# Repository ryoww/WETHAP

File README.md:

[WETHAPのサイト](https://ryoww.github.io/WETHAP/)
実験室の温度・湿度・気圧を教えてくれるツステム

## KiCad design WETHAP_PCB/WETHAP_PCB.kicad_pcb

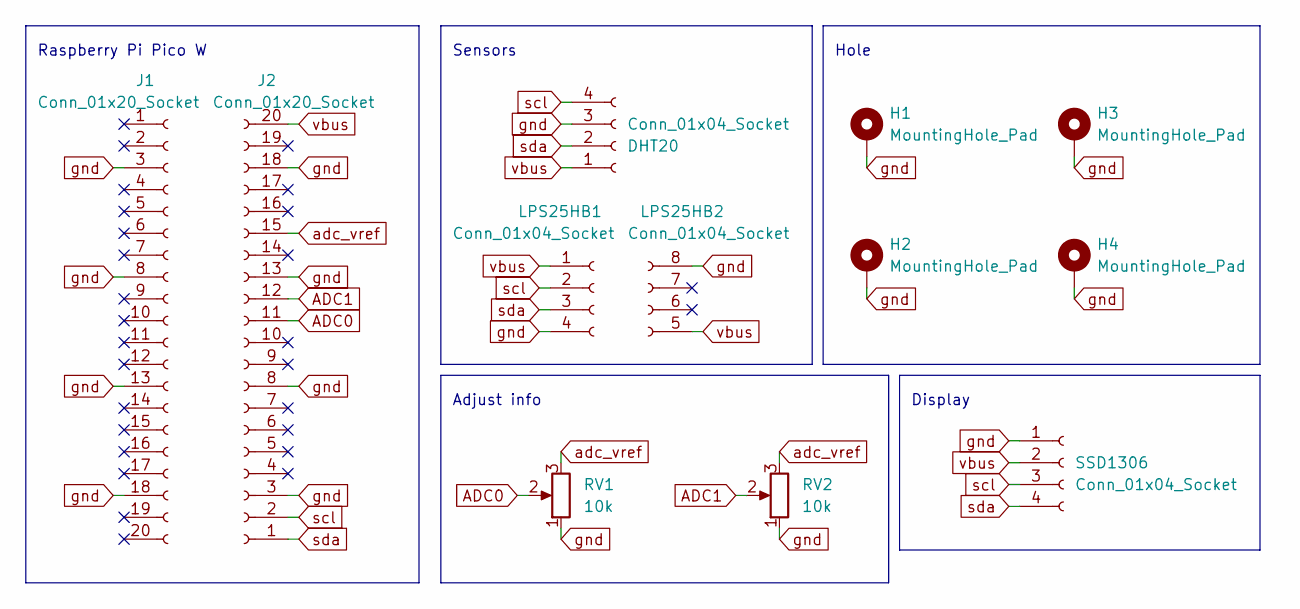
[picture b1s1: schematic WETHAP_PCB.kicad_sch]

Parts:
DHT20: Conn_01x04_Socket; PinSocket_1x04_P2.54mm_Vertical
H1, H2, H3, H4: MountingHole_Pad; MountingHole_3.2mm_M3_DIN965_Pad
J1, J2: Conn_01x20_Socket; PinSocket_1x20_P2.54mm_Vertical
LPS25HB1, LPS25HB2: Conn_01x04_Socket; PinSocket_1x04_P2.54mm_Vertical
RV1, RV2: 10k; Potentiometer_Bourns_3296W_Vertical
SSD1306: Conn_01x04_Socket; PinSocket_1x04_P2.54mm_Vertical

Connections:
ADC0: J2.11, RV1.2
ADC1: J2.12, RV2.2
adc_vref: J2.15, RV1.3, RV2.3
gnd: DHT20.3, H1.1, H2.1, H3.1, H4.1, J1.3, J1.8, J1.13, J1.18, J2.3, J2.8, J2.13, J2.18, LPS25HB1.4, LPS25HB2.8 (Pin_4), RV1.1, RV2.1, SSD1306.1
scl: DHT20.4, J2.2, LPS25HB1.2, SSD1306.3
sda: DHT20.2, J2.1, LPS25HB1.3, SSD1306.4
vbus: DHT20.1, J2.20, LPS25HB1.1, LPS25HB2.5 (Pin_1), SSD1306.2

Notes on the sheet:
Adjust info
Raspberry Pi Pico W
Display
Hole
Sensors

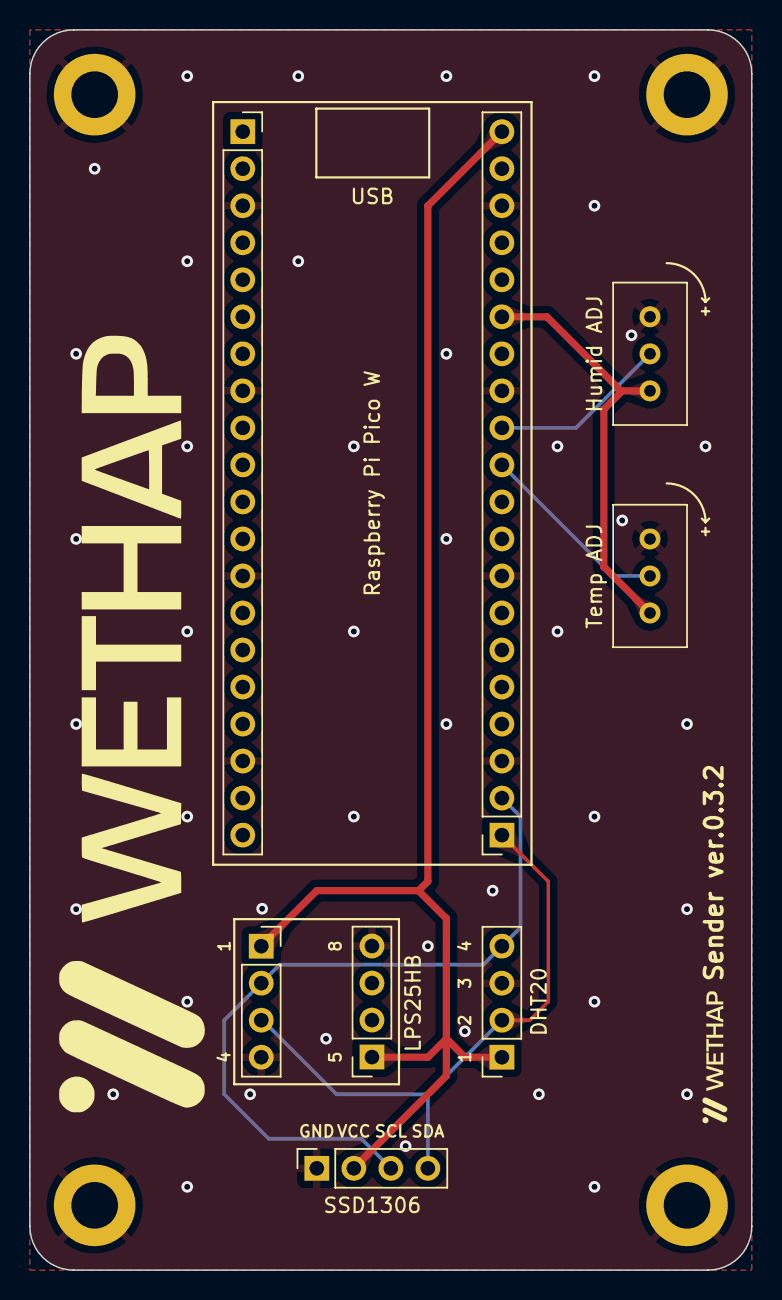
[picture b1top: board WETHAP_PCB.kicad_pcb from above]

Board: 2 copper layers, 49.5 x 85.1 mm, 14 parts (0 on the bottom side), 7 nets.

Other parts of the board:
G0: LOGO; WETHAP_logo
G1: LOGO; logo

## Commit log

2023-02-25 test
2023-02-25 APIサーバの基本形作った
2023-02-25 add requirements.txt
2023-02-25 ちょっと変更
2023-02-25 test update
2023-02-25 Revert "add requirements.txt"
    This reverts commit 1370e004240a82fe8575f0ab90543c8176910adb.
2023-02-25 add app.py
2023-03-01 update: main.py
    create: postdata.py
    add: requirements.txt
2023-03-10 add read-all.py & app.py
2023-03-10 インデント修正 app.py
2023-03-14 add key.pyapp.pyを辛うじて動くようにした今後は研究室名が無かったら送らせる＆情報作成
2023-03-16 add fetch_info.py
2023-03-16 aaaa
2023-03-16 返り血でdictで返すようにした
2023-03-16 state == 2を改良
2023-03-20 SQLiteのexecuteメソッドでSQL文を実行して書き込んでいくスタイルに変えようと企んでいる
2023-03-20 read-all.py最新版
2023-03-20 クエリでfetchするようにした
2023-03-20 URL修正
2023-04-08 sqliteでDB保存の試み
2023-04-09 SQL化できた
2023-04-09 とりあえずid関連の関数作成呼び出しとかもろもろがまだ
2023-04-11 APIにエンドポイント追加: DBの中身閲覧, 研究室が登録されているか
2023-04-11 とりあえずサブミット
2023-04-11 とりあえずサブミットパート２
2023-04-11 db更新
2023-04-11 db更新パート2
2023-04-14 try-exceptのコメントアウト外しただけ
2023-04-29 DBバックアップ(20230429)
2023-04-29 サーバ側で天気を取得するようした
2023-05-03 add assets
2023-05-04 update assets
2023-05-04 DBバックアップ(20230504)
2023-05-07 cache削除
2023-05-07 ごにょごにょ
2023-05-07 register
2023-05-07 add gitignore
2023-05-07 gitignore適用！
2023-05-07 init
2023-05-09 db fix
2023-05-09 update datetime format
2023-05-09 test;;
2023-05-09 送信端末用仮完成
2023-05-09 コード整理 & typo fix
2023-05-09 OLED焼き付き防止
2023-05-09 fix display log
2023-05-10 add i2c init sleep
    デバッグしてない
2023-05-10 optimize
2023-05-10 typo fix
2023-05-10 various fix
2023-05-10 finish_time fix
2023-05-11 time update without ntp
2023-05-11 update???
2023-05-12 再接続処理 & OLED表示クラス化
2023-05-13 update: gitignore
2023-05-13 ロード画面(簡易)
2023-05-13 エラー落ち回避
2023-05-14 i2cバス接続化 & テスト送信追加
2023-05-16 split class file
2023-05-17 wip env_collector
2023-05-17 responsive??
2023-05-20 dht11対応
2023-05-20 add typing
2023-05-20 pull up enable
2023-05-22 reboot when error
2023-05-23 backup database
2023-05-23 reset database
2023-05-24 bug fix
2023-05-26 running status on led
2023-05-26 DHT20 仮対応
2023-06-10 update aep
2023-06-11 optimize reboot
2023-06-22 add prefix(/WETHAP/api) to all endpoints
2023-08-19 温湿度オフセット&基板設計
2023-08-19 update gbr,drl
2023-08-26 add logo
2023-09-14 app.pyからwethapLine.pyに機能を移行
2023-09-14 app.pyの機能をwethapLine.pyにパージ
2023-09-15 wethapLine新しく作る
2023-09-16 最終的に返す関数実装
2023-09-17 一段階目とりあえず完成
2023-09-17 update sender logo
2023-09-22 add every_week_send
2023-09-24 add every_week
2023-09-25 今日のお昼ご飯はオムライス
2023-09-25 pcb v0.2.0
2023-10-25 fix circuit
2023-10-26 lps25hb support
2023-10-27 change api server url
2023-10-27 change server url
2023-10-27 build
2023-10-27 clean build
2023-10-27 fix api prefix
2023-10-27 fetch_info cafe update
2023-11-01 env file
2023-11-05 renewal api
2023-11-05 fix bug
2023-11-14 graceful shutdown
2023-11-17 db error handle
2023-11-22 add remove
2023-12-08 update psycopg
2023-12-08 fix fetchone
2023-12-10 change file tree
2023-12-10 update requirements
2023-12-10 fix previewData
2023-12-11 change host
2023-12-11 daemon
2023-12-17 add request info
2023-12-17 websocket
2023-12-17 fix request info message
2023-12-17 no display tasks
2023-12-17 add env sample
2023-12-18 fix pcb
2023-12-18 handshake status led
2023-12-19 update api server url
2023-12-19 keep connection
2023-12-19 ws_manager bug fix
2023-12-19 dummy sender labID
2023-12-19 get all labID bug fix
2023-12-20 update sender update
2023-12-20 dict_cursor
2023-12-20 fix wrap
2023-12-20 snake case in db
2023-12-20 snake case for db
2023-12-20 remove debug message
2023-12-20 fix http api
2023-12-21 snake case
2023-12-21 Revert "snake case for db"
    This reverts commit 75884693ac2dc236b4148efd8369af862dc10960.
2023-12-21 change labID
2023-12-21 change labID and bug fix
2024-01-09 reset when exception
2024-01-12 ws bug fix
2024-01-14 error handle
2024-01-15 fix bug?
2024-01-15 fix display
2024-01-16 change info send format
2024-01-16 keep alive
2024-01-22 update naming rules
2024-01-28 change endpoint
2024-05-06 feature: receive sender response when request info
2024-05-06 refactor: fetch weather move to utils
2024-05-06 feature: auto install ssd1306 package
2024-05-06 fix: fetch weather
2024-05-06 add: add time column to infos table
2024-05-06 feature: time column
2024-05-06 feature: add time to manual info
2024-05-06 fix: remove 204 status code
2024-05-06 fix: change labID
2024-05-06 update: ws manager's active rooms converted to a property
2024-05-06 fix: error when changing from non exist labID
2024-05-07 fix: fetch weather error handling
2024-05-07 change: original DHT20 class
2024-05-07 docs: add license comment to ws.py
2024-05-07 feature: sender identifier name
2024-05-09 bug fix: syntax error in update query update: manual_db
2024-05-09 feature: get_rows endpoint
2024-05-09 fix: extra code
2024-05-10 fix: order is params
2024-05-10 feature: add select_one, select_all in TableManager
2024-05-10 fix: use select_all, select_one
2024-05-10 fix: select null query
2024-05-10 fix: queries SQL injection measure
2024-05-10 update: always send time
2024-05-10 change: use manual_infos table to get-rows
2024-05-10 update: /manual endpoint
2024-05-10 add: logger
2024-05-10 change: wrap record
2024-05-10 remove: /request, /get-rows endpoint
2024-05-10 fix: use uvicorn logger
2024-05-15 feature: delete all content in table
2024-08-18 chore: build gerber files
2024-08-18 fix: server side polling at manual
2024-08-23 fix: syntax error
2024-08-27 fix: decode labID when receive bytes
2024-08-27 fix: decode lab_id when receive bytes
2024-09-23 app.py update line-bot-sdk v3
2024-09-24 test rich_menu
2024-10-20 わからんupdate
2024-10-20 wakaranwakaran
2024-10-22 panel pdf ok
2024-10-22 Revert "panel pdf ok"
    This reverts commit 20f7def53daec60dc09d2e2106c69e787c6fb819.
